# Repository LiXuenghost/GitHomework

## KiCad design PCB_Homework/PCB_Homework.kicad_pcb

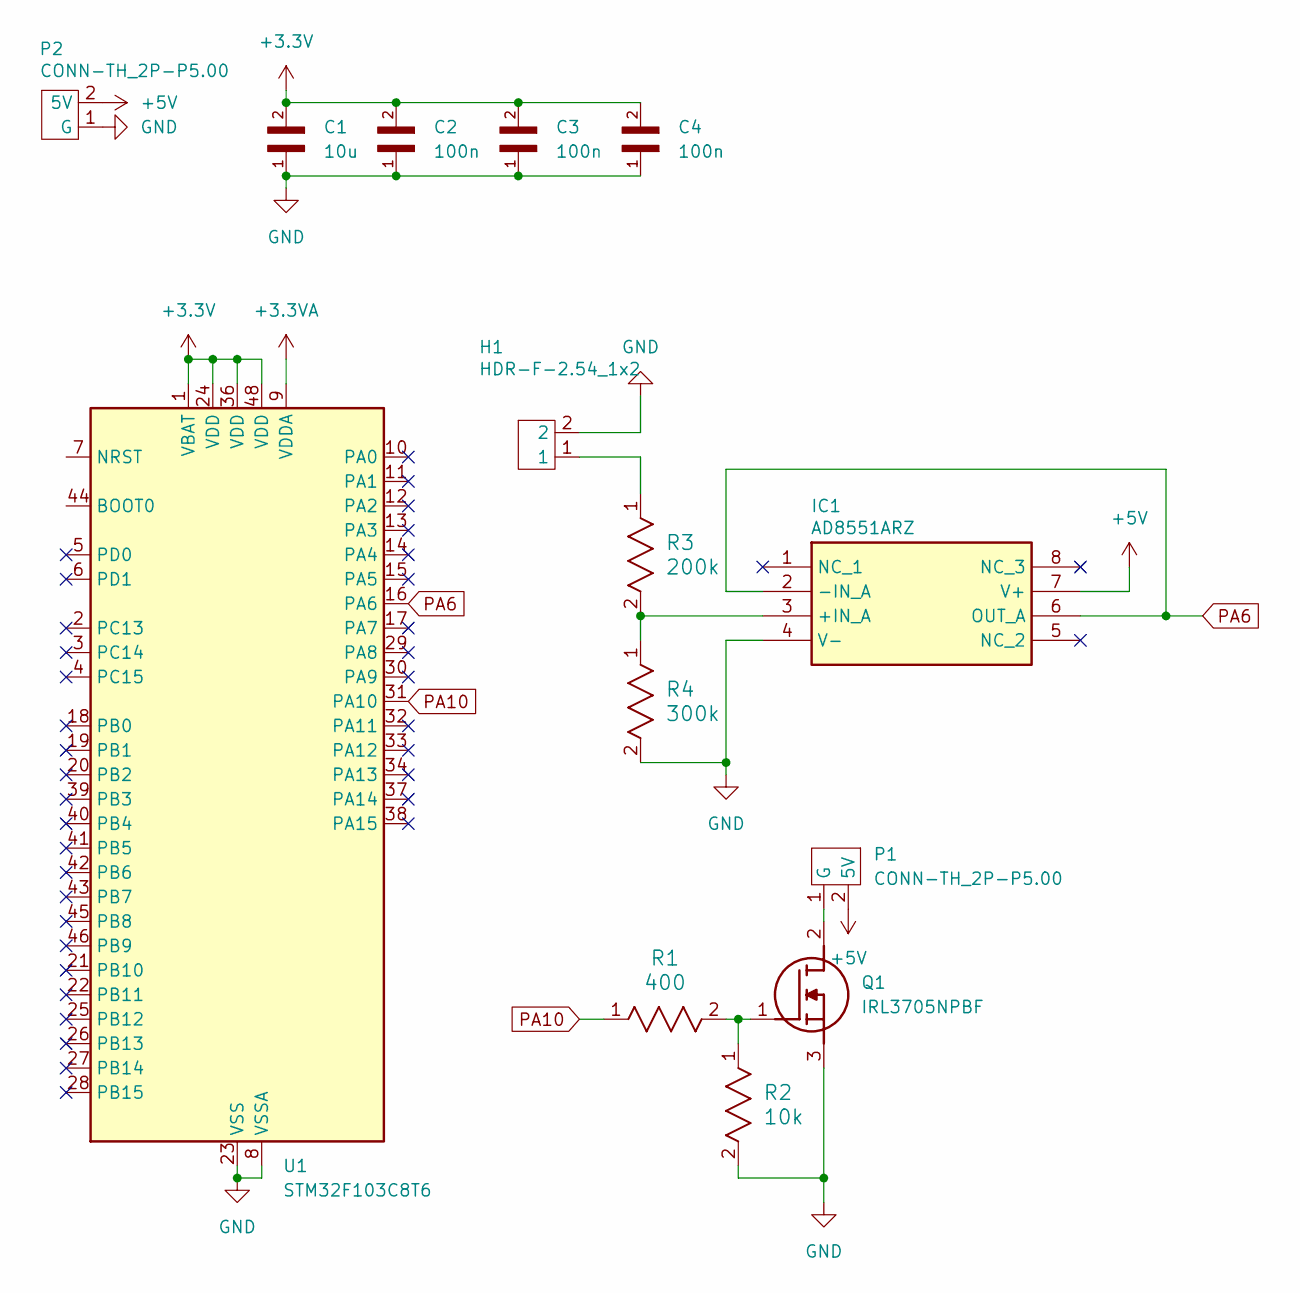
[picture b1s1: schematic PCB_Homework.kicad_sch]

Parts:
C1: 10u; Ceramic Capacitor
C2, C3, C4: 100n; Ceramic Capacitor
H1: HDR-F-2.54_1x2; CONN_PPPC021_SUL
IC1: AD8551ARZ; SOIC127P600X175-8N; Mouser Part Number 584-AD8551ARZ
P1, P2: CONN-TH_2P-P5.00
Q1: IRL3705NPBF; TO254P469X1042X1930-3P; Mouser Part Number 942-IRL3705NPBF
R1: 400; Resistor
R2: 10k; Resistor
R3: 200k; Resistor
R4: 300k; Resistor
U1: STM32F103C8T6; LQFP-48_7x7mm_P0.5mm

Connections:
+3.3V: C1.2, C2.2, C3.2, C4.2, U1.1 (VBAT), U1.24 (VDD), U1.36 (VDD), U1.48 (VDD)
+3.3VA: U1.9 (VDDA)
+5V: IC1.7 (V+), P1.2 (5V), P2.2 (5V)
GND: C1.1, C2.1, C3.1, C4.1, H1.2, IC1.4 (V-), P2.1 (G), Q1.3 (S), R2.2, R4.2, U1.8 (VSSA), U1.23 (VSS), U1.35 (VSS), U1.47 (VSS)
unnamed: H1.1, R3.1
unnamed: IC1.3 (+IN_A), R3.2, R4.1
unnamed: P1.1 (G), Q1.2 (D)
unnamed: Q1.1 (G), R1.2, R2.1
PA6: IC1.2 (-IN_A), IC1.6 (OUT_A), U1.16 (PA6)
PA10: R1.1, U1.31 (PA10)

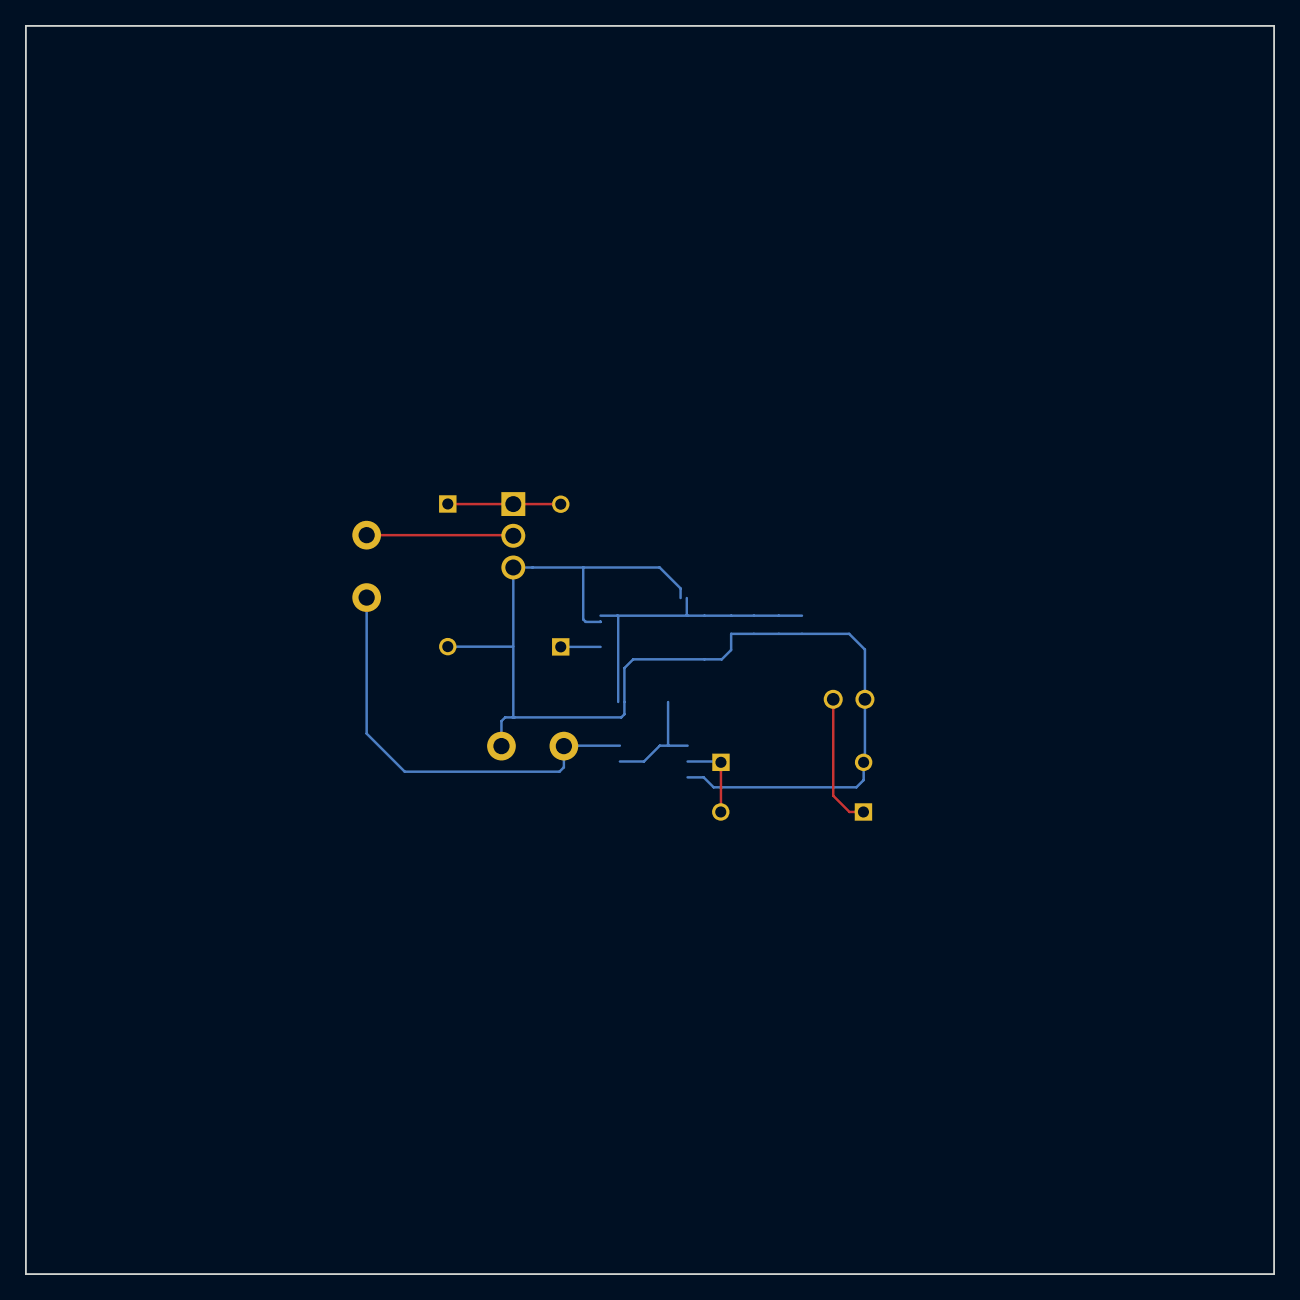
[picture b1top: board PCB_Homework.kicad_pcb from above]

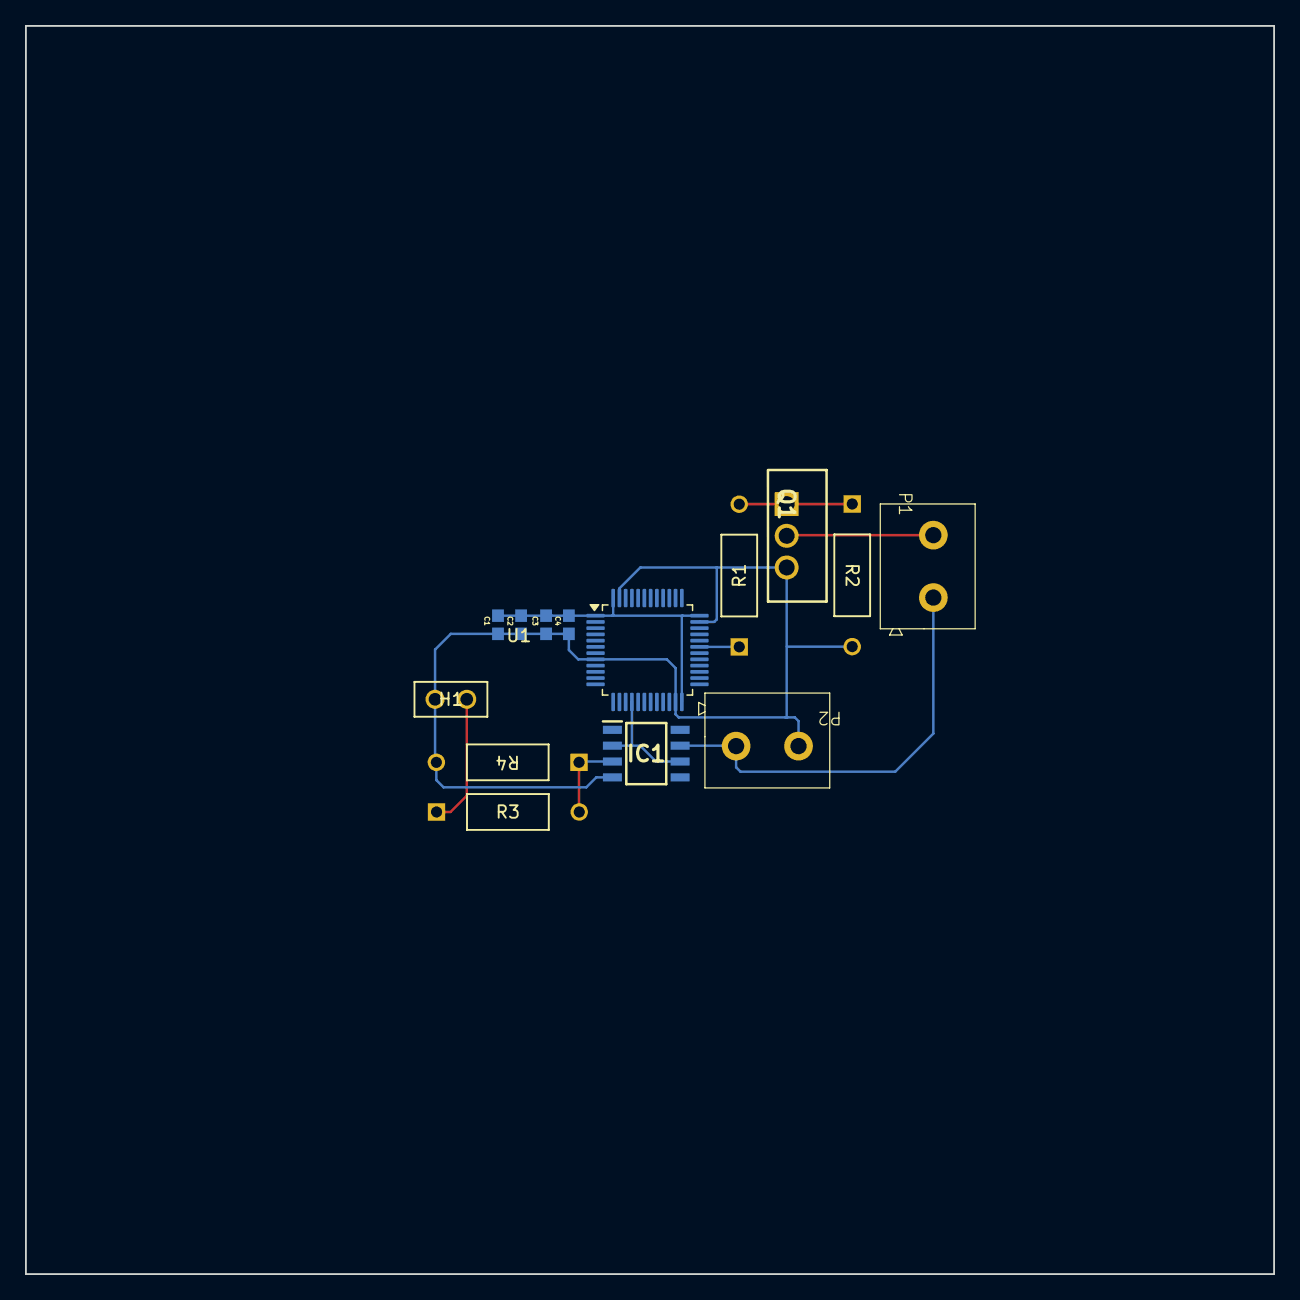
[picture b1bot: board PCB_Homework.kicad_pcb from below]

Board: 2 copper layers, 100.0 x 100.0 mm, 14 parts (14 on the bottom side), 9 nets.

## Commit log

2026-02-25 Finish
2026-02-28 Add the PCB Homework
2026-02-28 Commit PCB file
2026-02-28 Electronic_HW
